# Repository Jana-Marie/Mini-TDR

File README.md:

# Mini-TDR

Software defined TDR based on an STM32G474, MCU+USB interface work and are tested, TDR AFE is untested. Firmware needs to be updated.

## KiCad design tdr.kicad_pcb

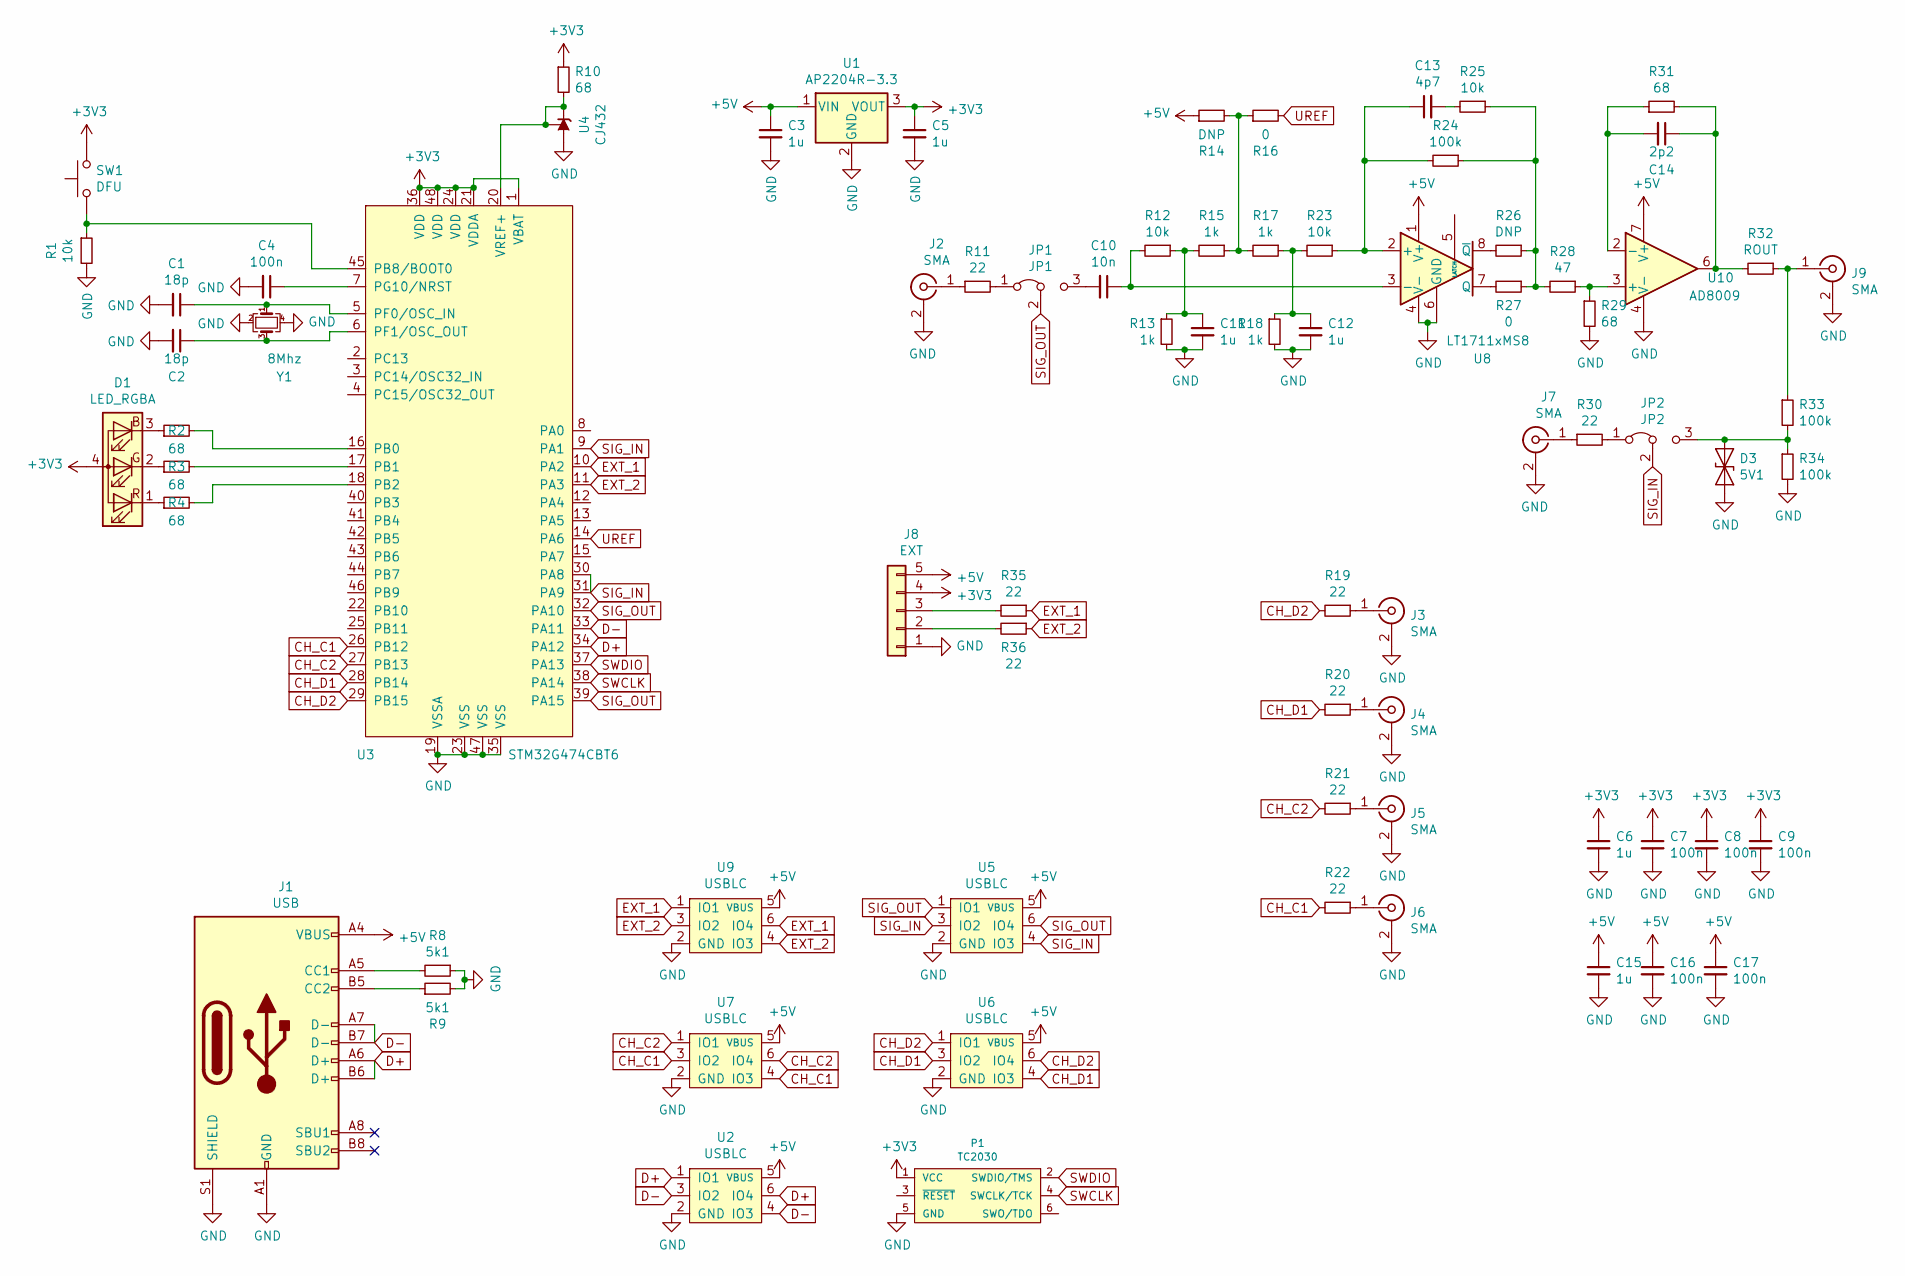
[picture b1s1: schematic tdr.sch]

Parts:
C1, C2: 18p; C_0402
C3, C5, C6, C11, C12, C15: 1u; C_0603
C4, C7, C8, C9, C16, C17: 100n; C_0402
C10: 10n; C_0402
C13: 4p7; C_0402
C14: 2p2; C_0402
D1: LED_RGBA; LED_Avago_PLCC4_3.2x2.8mm_CW
D3: 5V1; D_SOD-123F
J1: USB; USB-C 16Pin
J2, J3, J4, J5, J6, J7: SMA; SMA_Amphenol_132291_Vertical
J8: EXT; JST_PH_B5B-PH-K_1x05_P2.00mm_Vertical
J9: SMA; SMA_Amphenol_132289_EdgeMount
JP1: JP1; PinHeader_1x03_P2.54mm_Vertical
JP2: JP2; PinHeader_1x03_P2.54mm_Vertical
P1: TC2030
R1, R12, R23, R25: 10k; R_0402
R2, R3, R4, R10, R29, R31: 68; R_0402
R8, R9: 5k1; R_0402
R11, R19, R20, R21, R22, R30, R35, R36: 22; R_0402
R13, R15, R17, R18: 1k; R_0402
R14, R26: DNP; R_0402
R16, R27: 0; R_0402
R24, R33, R34: 100k; R_0402
R28: 47; R_0402
R32: ROUT; R_0805
SW1: DFU; SW_SPST_PTS810
U1: AP2204R-3.3; SOT-89-3
U2, U5, U6, U7, U9: USBLC; SOT-23-6
U3: STM32G474CBT6; TQFP-48_7x7mm_P0.5mm
U4: CJ432; SOT-23
U8: LT1711xMS8; MSOP-8_3x3mm_P0.65mm
U10: AD8009; SOIC-8_3.9x4.9mm_P1.27mm
Y1: 8Mhz; Crystal_SMD_3225-4Pin_3.2x2.5mm

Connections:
+3V3: C5.1, C6.1, C7.1, C8.1, C9.1, D1.4 (A), J8.4, P1.1 (VCC), R10.1, SW1.2, U1.3 (VOUT), U3.1 (VBAT), U3.21 (VDDA), U3.24 (VDD), U3.36 (VDD), U3.48 (VDD)
+5V: C3.1, C15.1, C16.1, C17.1, J1.A4 (VBUS), J1.A9 (VBUS), J1.B4 (VBUS), J1.B9 (VBUS), J8.5, R14.1, U1.1 (VIN), U2.5 (VBUS), U5.5 (VBUS), U6.5 (VBUS), U7.5 (VBUS), U8.1 (V+), U9.5 (VBUS), U10.7 (V+)
CH_C1: R22.2, U3.26 (PB12), U7.3 (IO2), U7.4 (IO3)
CH_C2: R21.2, U3.27 (PB13), U7.1 (IO1), U7.6 (IO4)
CH_D1: R20.2, U3.28 (PB14), U6.3 (IO2), U6.4 (IO3)
CH_D2: R19.2, U3.29 (PB15), U6.1 (IO1), U6.6 (IO4)
D+: J1.A6 (D+), J1.B6 (D+), U2.1 (IO1), U2.6 (IO4), U3.34 (PA12)
D-: J1.A7 (D-), J1.B7 (D-), U2.3 (IO2), U2.4 (IO3), U3.33 (PA11)
EXT_1: R35.1, U3.10 (PA2), U9.1 (IO1), U9.6 (IO4)
EXT_2: R36.1, U3.11 (PA3), U9.3 (IO2), U9.4 (IO3)
GND: C1.2, C2.2, C3.2, C4.2, C5.2, C6.2, C7.2, C8.2, C9.2, C11.2, C12.2, C15.2, C16.2, C17.2, D3.2 (A2), J1.A1 (GND), J1.A12 (GND), J1.B1 (GND), J1.B12 (GND), J1.S1 (SHIELD), J2.2 (Ext), J3.2 (Ext), J4.2 (Ext), J5.2 (Ext), J6.2 (Ext), J7.2 (Ext), J8.1, J9.2 (Ext), P1.5 (GND), R1.2, R8.1, R9.2, R13.2, R18.2, R29.2, R34.2, U1.2 (GND), U2.2 (GND), U3.19 (VSSA), U3.23 (VSS), U3.35 (VSS), U3.47 (VSS), U4.3 (A), U5.2 (GND), U6.2 (GND), U7.2 (GND), U8.4 (V-), U8.6 (GND), U9.2 (GND), U10.4 (V-), Y1.2, Y1.4
unnamed: C1.1, U3.5 (PF0/OSC_IN), Y1.1
unnamed: C2.1, U3.6 (PF1/OSC_OUT), Y1.3
unnamed: C4.1, U3.7 (PG10/NRST)
unnamed: C10.1, R12.2, U8.3 (-)
unnamed: C10.2, JP1.3 (B)
unnamed: C11.1, R12.1, R13.1, R15.2
unnamed: C12.1, R17.1, R18.1, R23.2
unnamed: C13.1, R23.1, R24.2, U8.2 (+)
unnamed: C13.2, R25.2
unnamed: C14.1, R31.2, R32.2, U10.6
unnamed: C14.2, R31.1, U10.2 (-)
unnamed: D1.1 (RK), R4.1
unnamed: D1.2 (GK), R3.1
unnamed: D1.3 (BK), R2.1
unnamed: D3.1 (A1), JP2.3 (B), R33.2, R34.1
unnamed: J1.A5 (CC1), R8.2
unnamed: J1.B5 (CC2), R9.1
unnamed: J2.1 (In), R11.1
unnamed: J3.1 (In), R19.1
unnamed: J4.1 (In), R20.1
unnamed: J5.1 (In), R21.1
unnamed: J6.1 (In), R22.1
unnamed: J7.1 (In), R30.1
unnamed: J8.2, R36.2
unnamed: J8.3, R35.2
unnamed: J9.1 (In), R32.1, R33.1
unnamed: JP1.1 (A), R11.2
unnamed: JP2.1 (A), R30.2
unnamed: R1.1, SW1.1, U3.45 (PB8/BOOT0)
unnamed: R2.2, U3.16 (PB0)
unnamed: R3.2, U3.17 (PB1)
unnamed: R4.2, U3.18 (PB2)
unnamed: R10.2, U3.20 (VREF+), U4.1 (REF), U4.2 (K)
unnamed: R14.2, R15.1, R16.1, R17.2
unnamed: R24.1, R25.1, R26.1, R27.1, R28.2
unnamed: R26.2, U8.8 (~Q)
unnamed: R27.2, U8.7 (Q)
unnamed: R28.1, R29.1, U10.3 (+)
SIG_IN: JP2.2 (C), U3.9 (PA1), U3.30 (PA8), U3.31 (PA9), U5.3 (IO2), U5.4 (IO3)
SIG_OUT: JP1.2 (C), U3.32 (PA10), U3.39 (PA15), U5.1 (IO1), U5.6 (IO4)
SWCLK: P1.4 (SWCLK/TCK), U3.38 (PA14)
SWDIO: P1.2 (SWDIO/TMS), U3.37 (PA13)
UREF: R16.2, U3.14 (PA6)

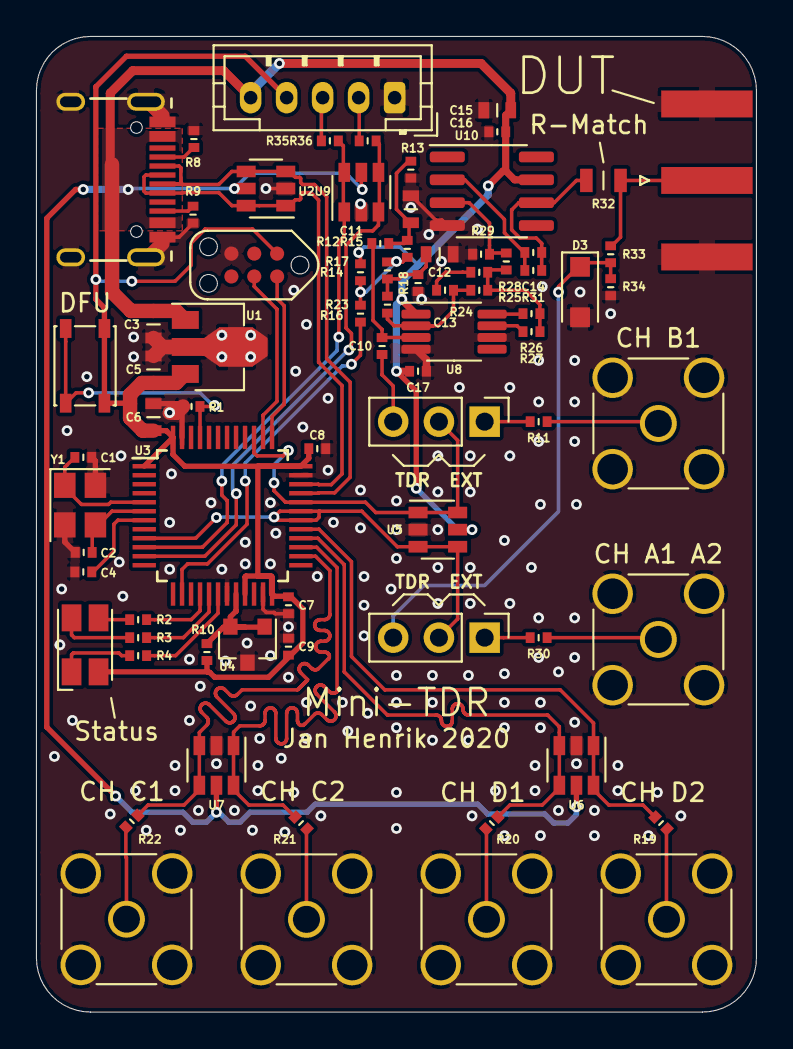
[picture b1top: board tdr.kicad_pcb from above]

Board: 2 copper layers, 40.0 x 54.2 mm, 76 parts (0 on the bottom side), 54 nets.

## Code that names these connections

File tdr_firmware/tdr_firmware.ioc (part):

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Mcu.Name=STM32G474C(B-C-E)Tx
Mcu.Package=LQFP48
Mcu.UserName=STM32G474CBTx
PA1.Mode=INP
PA1.Signal=COMP1_INP
PA10.Mode=Output_TB1
PA10.Signal=HRTIM1_CHB1
PA11.Mode=Device
PA11.Signal=USB_DM
PA12.Mode=Device
PA12.Signal=USB_DP
PA13.Mode=Serial_Wire
PA13.Signal=SYS_JTMS-SWDIO
PA14.Mode=Serial_Wire
PA14.Signal=SYS_JTCK-SWCLK
PA6.Signal=COMP_DAC21_group
PA8.Mode=Output_TA1TA2
PA8.Signal=HRTIM1_CHA1
PA9.Mode=Output_TA1TA2
PA9.Signal=HRTIM1_CHA2
PB12.Mode=Output_TC1TC2
PB12.Signal=HRTIM1_CHC1
PB13.Mode=Output_TC1TC2
PB13.Signal=HRTIM1_CHC2
PB14.Mode=Output_TD1TD2
PB14.Signal=HRTIM1_CHD1
PB15.Mode=Output_TD1TD2
PB15.Signal=HRTIM1_CHD2
PF0-OSC_IN.Mode=HSE-External-Oscillator
PF0-OSC_IN.Signal=RCC_OSC_IN
PF1-OSC_OUT.Mode=HSE-External-Oscillator
PF1-OSC_OUT.Signal=RCC_OSC_OUT
RCC.HSE_VALUE=8000000
RCC.SYSCLKFreq_VALUE=168000000
RCC.SYSCLKSource=RCC_SYSCLKSOURCE_PLLCLK
board=custom

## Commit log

2020-09-27 added gitignore
2020-09-27 added image
2021-02-13 added schematic, updated fw
